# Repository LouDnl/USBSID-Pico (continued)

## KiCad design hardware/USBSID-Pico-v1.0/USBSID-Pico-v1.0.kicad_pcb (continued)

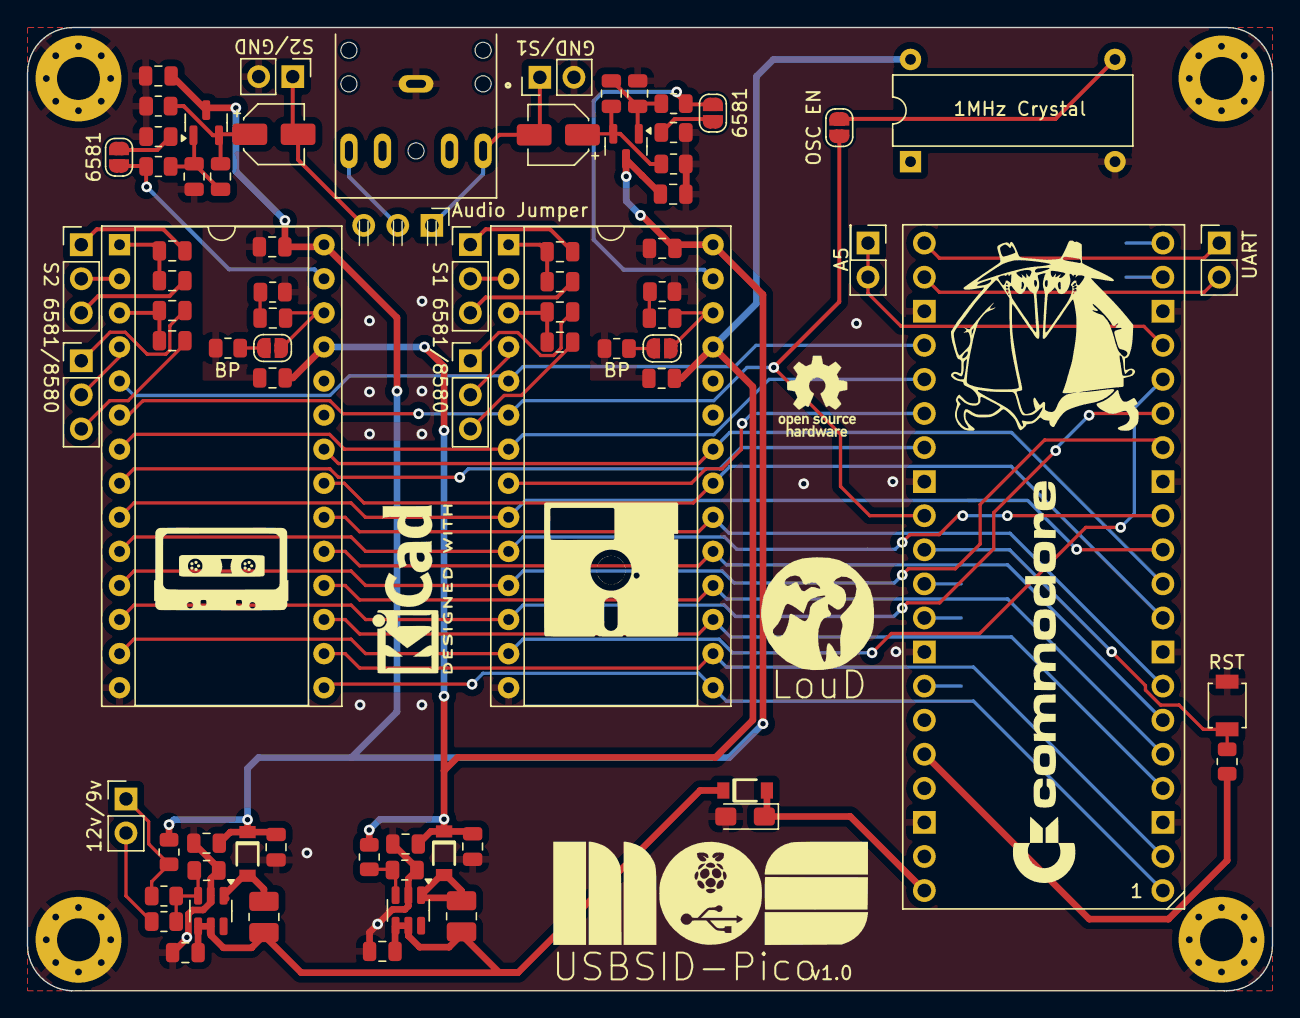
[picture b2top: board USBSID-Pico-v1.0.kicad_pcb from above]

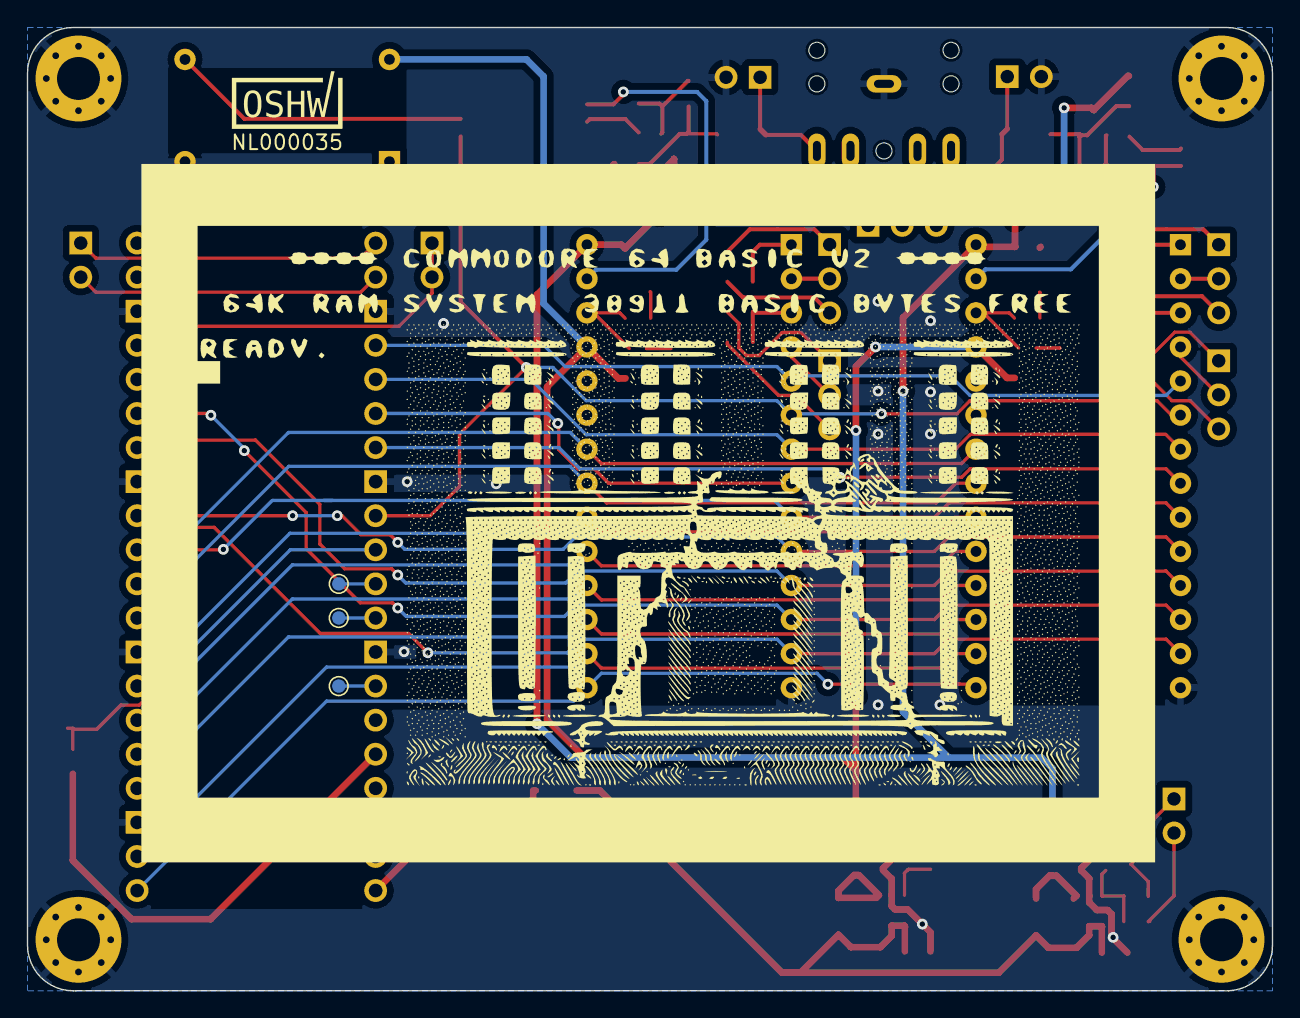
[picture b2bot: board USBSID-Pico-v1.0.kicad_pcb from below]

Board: 2 copper layers, 92.8 x 71.8 mm, 85 parts (5 on the bottom side), 73 nets.

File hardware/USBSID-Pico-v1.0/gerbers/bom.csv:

"Reference","Value","Mfg Qty","Mfg Part #","Manufacturer","Mfg Part Desc","Datasheet","Footprint","Optional Part #","Optional datasheet"
"TP1,TP2,TP3,TP4,TP5","-- mixed values --","","","","","~","TestPoint:TestPoint_Pad_D1.0mm","",""
"C1","10uF","1","T491A106K016AT","KEMET","10uF 16V 3Ω@100kHz ±10% CASE-A-3216-18(mm) Tantalum Capacitors","https://eu.mouser.com/datasheet/2/447/KEM_T2005_T491-3316937.pdf","Capacitor_Tantalum_SMD:CP_EIA-3216-10_Kemet-I_Pad1.58x1.35mm_HandSolder","",""
"C2,C4,C6,C8,C26,C27","470pF","1","0805B471K500NT","Guangdong Fenghua Advanced Tech","50V 470pF X7R ±10% 0805 Multilayer Ceramic Capacitors MLCC - SMD/SMT ROHS","https://www.lcsc.com/datasheet/lcsc_datasheet_2304140030_FH-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","Capacitor_SMD:C_0805_2012Metric","",""
"C3,C5,C7,C9","22nF","1","CL21B223KBANNNC","Samsung","50V 22nF X7R ±10% 0805 Multilayer Ceramic Capacitors MLCC - SMD/SMT ROHS","https://www.lcsc.com/datasheet/lcsc_datasheet_2304140030_Sam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","Capacitor_SMD:C_0805_2012Metric","",""
"C10,C11","1000pF","1","CL21B102KBANNNC","Samsung","50V 1nF X7R ±10% 0805 Multilayer Ceramic Capacitors MLCC - SMD/SMT ROHS","https://www.lcsc.com/datasheet/lcsc_datasheet_2304140030_Sam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","Capacitor_SMD:C_0805_2012Metric","",""
"C12,C13,C18,C19,C22,C23,C24,C25","100nF","1","CL21B104KBCNNNC","Samsung","50V 100nF X7R ±10% 0805 Multilayer Ceramic Capacitors MLCC - SMD/SMT ROHS","https://www.lcsc.com/datasheet/lcsc_datasheet_2304140030_Sam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","Capacitor_SMD:C_0805_2012Metric","",""
"C14,C15","10uF","1","RVT1E100M0405","Honor Elec","10uF 25V ±20% SMD,D4xL5.4mm Aluminum Electrolytic Capacitors - SMD ROHS","https://www.lcsc.com/datasheet/lcsc_datasheet_2304140030_Hon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","Capacitor_SMD:CP_Elec_4x5.3","",""
"C16,C17,C20,C21,C28,C29","22uF","1","CL21A226MAQNNNE","Samsung","25V 22uF X5R ±20% 0805 Multilayer Ceramic Capacitors MLCC - SMD/SMT ROHS","https://www.lcsc.com/datasheet/lcsc_datasheet_2304140030_Sam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","Capacitor_SMD:C_0805_2012Metric","",""
"D1,D2,D3","MBR120","1","MBR120VLSFT1G","onsemi","20V 300mV@1A 1A SOD-123FL Schottky Diodes ROHS","https://www.lcsc.com/datasheet/lcsc_datasheet_2210210200_ons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","LouD:SOD-123FL_diode","",""
"J1,J2","-- mixed values --","1","IC254V-12-28-0743-P1524","XFCN","28P DIP Round Hole -40℃~+105℃ 15.24mm 2.54mm DIP-28 IC / Transistor Socket ROHS","https://www.lcsc.com/datasheet/lcsc_datasheet_2108150330_XFC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","Package_DIP:DIP-28_W15.24mm_Socket","DS1010-32T1NX","https://www.lcsc.com/datasheet/lcsc_datasheet_1810281820_CON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"
"J5,J6,J7,J8","-- mixed values --","1","PH2.54-01-03PZD","XUNPU","Direct Insert Policy 2.5mm 6mm 3P -40℃~+105℃ 3mm 2.54mm Black Brass Single Row 1x3P Plugin,P=2.54mm Pin Headers ROHS","https://www.lcsc.com/datasheet/lcsc_datasheet_2401280925_XUN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","Connector_PinHeader_2.54mm:PinHeader_1x03_P2.54mm_Vertical","",""
"J9","Audio jumper","1","PH2.54-07-03PWD","XUNPU","Bend insert Policy 2.5mm 6mm 3P -40℃~+105℃ 2.54mm Black Brass Single Row 1x3P Push-Pull,P=2.54mm Pin Headers ROHS","https://www.lcsc.com/datasheet/lcsc_datasheet_2401281210_XUN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","Connector_PinHeader_2.54mm:PinHeader_1x03_P2.54mm_Horizontal","",""
"J11,J12,J13,J14,J16","-- mixed values --","1","PH2.54-01-02PZD","XUNPU","Direct Insert Policy 2.5mm 6mm 2P -40℃~+105℃ 3mm 2.54mm Black Brass Single Row 1x2P Plugin,P=2.54mm Pin Headers ROHS","https://www.lcsc.com/datasheet/lcsc_datasheet_2401281145_XUN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","-- mixed values --","",""
"J20","AudioJack2_Ground_Switch","1","SJ1-3525N","CuiDevices","Audio Jack with tip and ring switch","https://www.switchcraft.com/3-5mm-pc-horizontal-mount-jack-s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","LouD:3.5MM_SWITCHCRAFT_35RAPC4BHN2","PJ3F07-5P","https://www.lcsc.com/datasheet/lcsc_datasheet_2409272203_SHO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"
"L1,L2","4,7uH 1000mA","1","SPH252012H4R7MT","SunLord","1.25A 4.7uH ±20% 1.2A 1008 Power Inductors ROHS","https://www.lcsc.com/datasheet/lcsc_datasheet_2310251550_Sun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","Inductor_SMD:L_1008_2520Metric_Pad1.43x2.20mm_HandSolder","",""
"Q1,Q2","MMBT2222A","1","MMBT2222ALT1G","onsemi","40V 225mW 100@150mA,10V 600mA NPN SOT-23 Bipolar (BJT) ROHS","https://www.lcsc.com/datasheet/lcsc_datasheet_2304140030_ons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","Package_TO_SOT_SMD:SOT-23","",""
"R1,R4,R5","10k","1","0805W8F1002T5E","UNI-ROYAL","125mW Thick Film Resistors 150V ±100ppm/℃ ±1% 10kΩ 0805 Chip Resistor - Surface Mount ROHS","https://www.lcsc.com/datasheet/lcsc_datasheet_2206010216_UNI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","Resistor_SMD:R_0805_2012Metric","",""
"R2,R3,R6,R7,R8,R9,R15","1k","1","0805W8F1001T5E","-- mixed values --","-- mixed values --","https://www.lcsc.com/datasheet/lcsc_datasheet_2205311800_UNI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","Resistor_SMD:R_0805_2012Metric","",""
"R10","7,5k","1","0805W8F7501T5E","UNI-ROYAL","125mW Thick Film Resistors 150V ±100ppm/℃ ±1% 7.5kΩ 0805 Chip Resistor - Surface Mount ROHS","https://www.lcsc.com/datasheet/lcsc_datasheet_2205311830_UNI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","Resistor_SMD:R_0805_2012Metric","",""
"R11","18k","1","0805W8F1802T5E","UNI-ROYAL","125mW Thick Film Resistors 150V ±100ppm/℃ ±1% 18kΩ 0805 Chip Resistor - Surface Mount ROHS","https://www.lcsc.com/datasheet/lcsc_datasheet_2206010216_UNI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","Resistor_SMD:R_0805_2012Metric","",""
"R12","47k","1","0805W8F4702T5E","UNI-ROYAL","125mW Thick Film Resistors 150V ±100ppm/℃ ±1% 47kΩ 0805 Chip Resistor - Surface Mount ROHS","https://www.lcsc.com/datasheet/lcsc_datasheet_2206010200_UNI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","Resistor_SMD:R_0805_2012Metric","",""
"R13,R14","100k","1","0805W8F1003T5E","UNI-ROYAL","125mW Thick Film Resistors 150V ±100ppm/℃ ±1% 100kΩ 0805 Chip Resistor - Surface Mount ROHS","https://www.lcsc.com/datasheet/lcsc_datasheet_2205312316_UNI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","Resistor_SMD:R_0805_2012Metric","",""
"R16,R17","330k","1","0805W8F3303T5E","UNI-ROYAL","125mW Thick Film Resistors 150V ±100ppm/℃ ±1% 330kΩ 0805 Chip Resistor - Surface Mount ROHS","https://www.lcsc.com/datasheet/lcsc_datasheet_2205311830_UNI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","Resistor_SMD:R_0805_2012Metric","",""
"SW1","RST","1","B3U-1000P","Omron Electronics","2.5mm 1.6mm Round Button 50mA Standing paste 3mm SPST 153gf 12V SMD,2.5x3mm Tactile Switches ROHS","https://eu.mouser.com/datasheet/2/307/en-b3u-3615.pdf","LouD:SW_SPST_B3U-1000P_larger_pads","",""
"U2,U3","MT3608","1","MT3608","AeroSemi","High Efficiency 1.2MHz 2A Step Up Converter","https://www.olimex.com/Products/Breadboarding/BB-PWR-3608/re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","Package_TO_SOT_SMD:SOT-23-6","",""
"U1","Pico","2","PM254-1-20-Z-8.5","HCTL","2.54mm Single Row 3A Brass Alloy 20P","https://www.lcsc.com/datasheet/lcsc_datasheet_2306091006_HCT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","LouD:RPi_Pico_TH_PinRows_Only","",""

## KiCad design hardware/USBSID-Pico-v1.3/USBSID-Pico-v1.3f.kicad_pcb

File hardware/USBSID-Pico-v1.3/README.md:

# USBSID-Pico v1.3 PCB design files
This directory contains the open source KiCad design files for v1.3 of the USBSID-Pico pcb.  

# Gerbers
The gerber files are in the [gerbers](gerbers/) directory.

# OSHWA certification
  
[OSHW] NL000045 | Certified open source hardware | [oshwa.org/cert](https://certification.oshwa.org/nl000045.html)

# Disclaimer
I do this stuff in my free time for my enjoyment. Since I like to share my joy in creating this with everyone I try my best to provide a working PCB and Firmware. I am in no way an electronics engineer and can give __no guarantees__ that this stuff does not break or damage your hardware, computer, phone, or whatever you try to hook it up to. Be sure to take great care when inserting any real MOS SID chips into the board. While everything has been tested with real chips, this is in no way a guarantee that nothing could go wrong. Use of this board and firmware at your own risk! I am in no way responsible for your damaged hardware. That being said, have fun!

# License
### Software License ~ GNUv2
All code written by me in this repository is licensed under the terms of the GNU General Public License as published by the Free Software Foundation, version 2.
Any code in this repository that is not written by me automatically falls under the licensing conditions by the authors of said code as mentioned in the source code header.
For for more information about this license please read the LICENSE document in the root of the USBSID-Pico repository.
### USBSID-Pico v1.3 PCB Hardware License ~ CC BY-SA 4.0
<a href="https://github.com/LouDnl/USBSID-Pico/tree/master/hardware/USBSID-Pico-v1.3">USBSID-Pico v1.3 PCB</a> © 2025-2026 by <a href="https://github.com/LouDnl">LouD</a> is licensed under <a href="https://creativecommons.org/licenses/by-sa/4.0/">Creative Commons Attribution-ShareAlike 4.0 International</a>

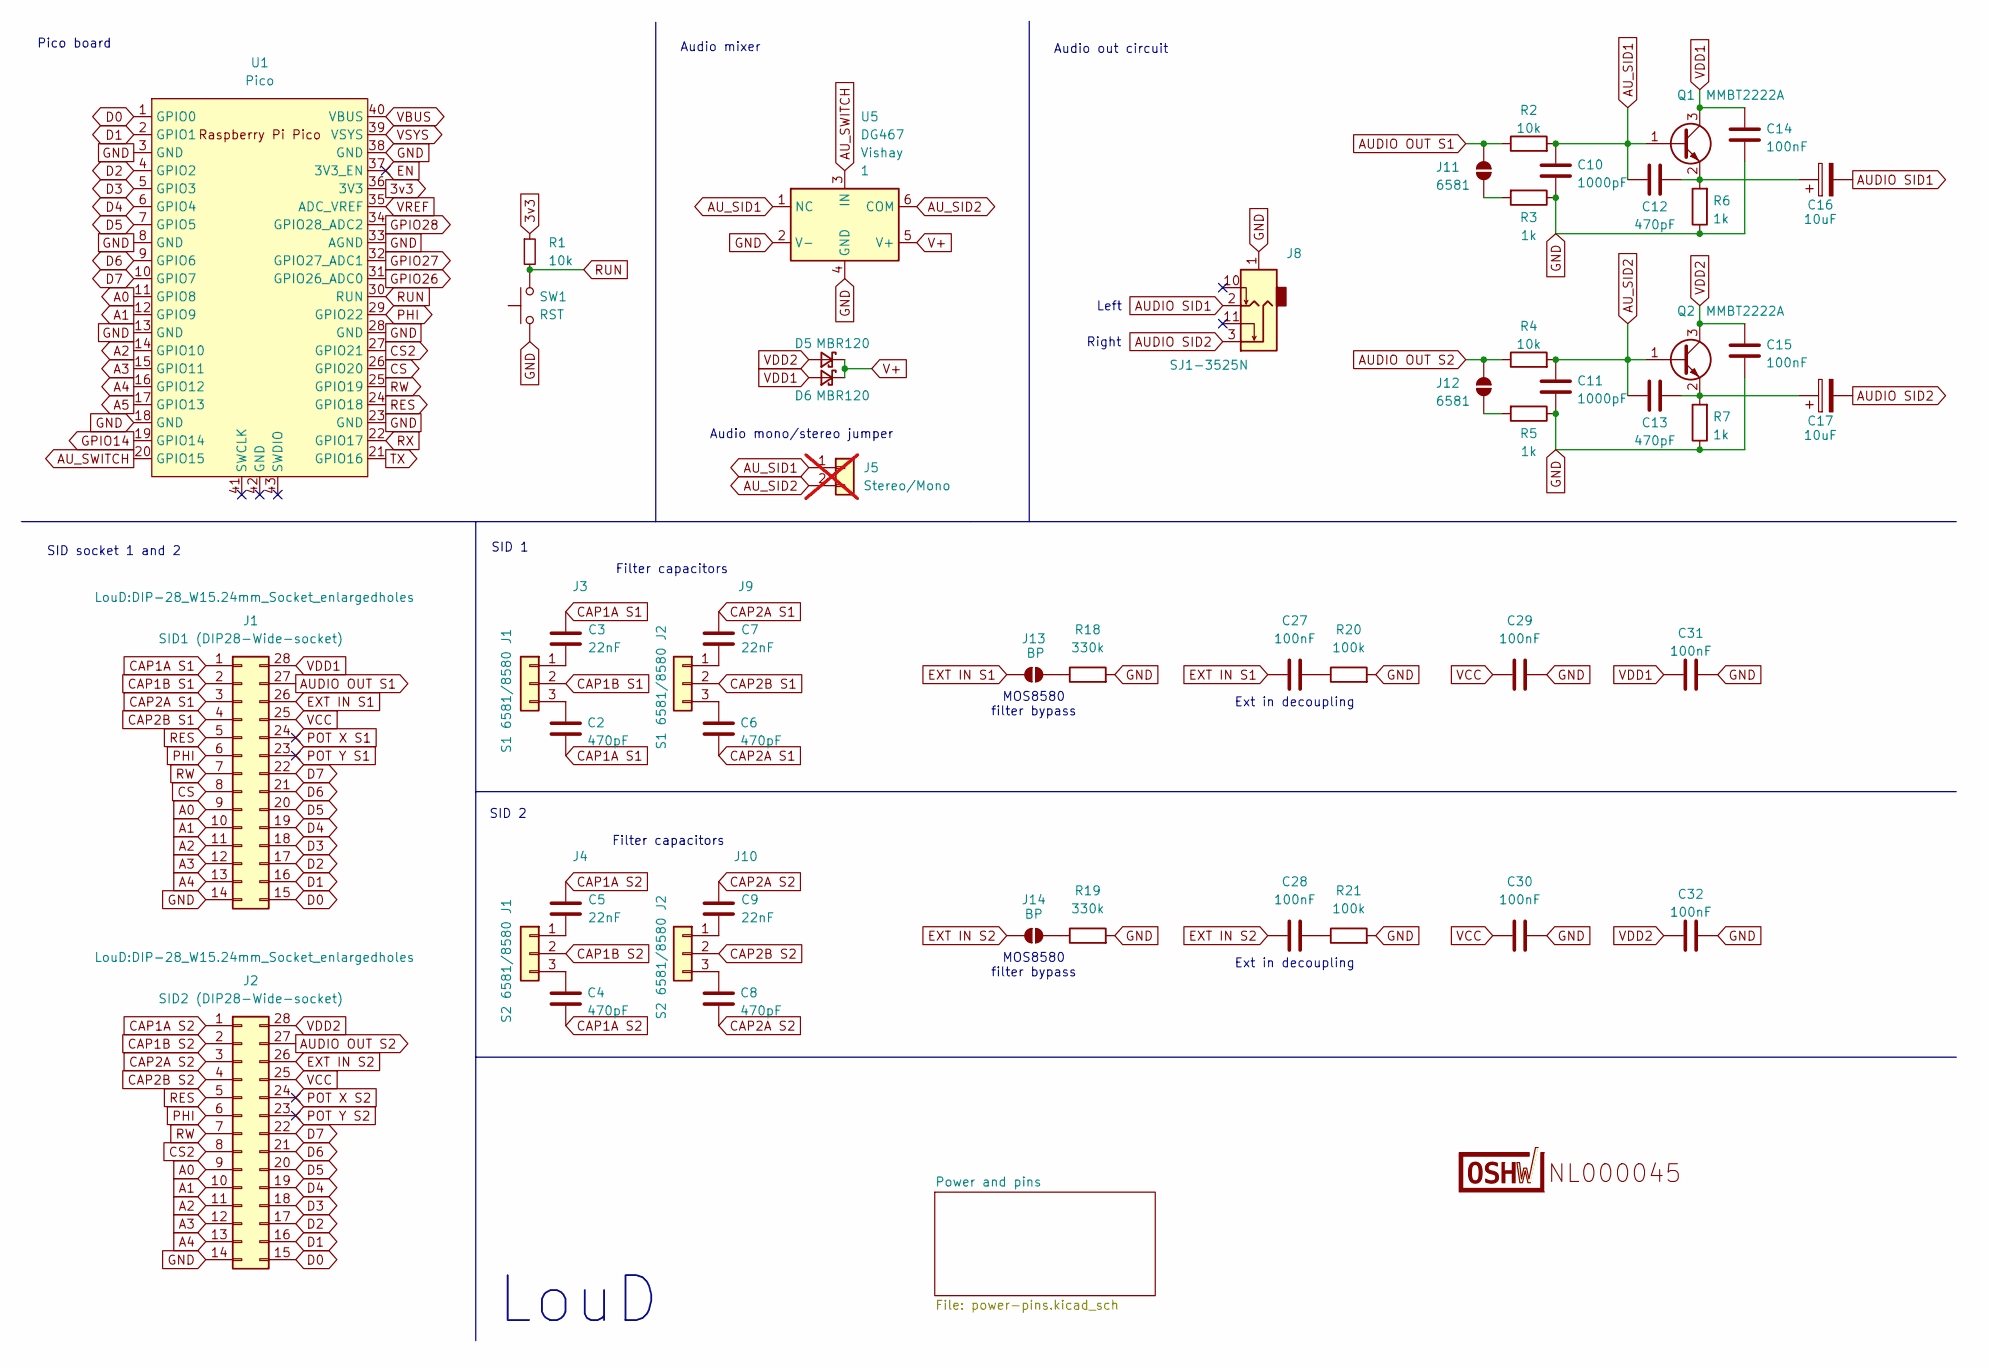
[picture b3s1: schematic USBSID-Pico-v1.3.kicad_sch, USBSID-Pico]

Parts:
C2, C4, C6, C8, C12, C13: 470pF; C_0805_2012Metric; Mfg Part # 0805B471K500NT
C3, C5, C7, C9: 22nF; C_0805_2012Metric; Mfg Part # CL21B223KBANNNC
C10, C11: 1000pF; C_0805_2012Metric; Mfg Part # CL21B102KBANNNC
C14, C15, C27, C28, C29, C30, C31, C32: 100nF; C_0805_2012Metric; Mfg Part # CL21B104KBCNNNC
C16, C17: 10uF; CP_Elec_4x5.3; Mfg Part # RVT1E100M0405
D5, D6: MBR120; SOD-123FL_diode; Mfg Part # MBR120VLSFT1G
J1: SID1 (DIP28-Wide-socket); DIP-28_W15.24mm_Socket_enlargedholes; Mfg Part # DS1009-28AT1WX-0A2
J2: SID2 (DIP28-Wide-socket); DIP-28_W15.24mm_Socket_enlargedholes; Mfg Part # DS1009-28AT1WX-0A2
J3: S1 6581/8580 J1; PinHeader_1x03_P2.54mm_Horizontal; Mfg Part # HX PZ2.54-1x3P WZ
J4: S2 6581/8580 J1; PinHeader_1x03_P2.54mm_Horizontal; Mfg Part # HX PZ2.54-1x3P WZ
J5: Stereo/Mono; PinHeader_1x02_P2.54mm_Horizontal; Mfg Part # PH2.54-01-02PZD; not fitted
J8: SJ1-3525N; 3.5MM_SWITCHCRAFT_35RAPC4BHN2; Mfg Part # SJ1-3525N
J9: S1 6581/8580 J2; PinHeader_1x03_P2.54mm_Horizontal; Mfg Part # HX PZ2.54-1x3P WZ
J10: S2 6581/8580 J2; PinHeader_1x03_P2.54mm_Horizontal; Mfg Part # HX PZ2.54-1x3P WZ
J11, J12: 6581; SolderJumper-2_P1.3mm_Open_RoundedPad1.0x1.5mm
J13, J14: BP; SolderJumper-2_P1.3mm_Open_RoundedPad1.0x1.5mm
LOGO1: (no value)
Q1, Q2: MMBT2222A; SOT-23; Mfg Part # MMBT2222ALT1G
R1, R2, R4: 10k; R_0805_2012Metric; Mfg Part # 0805W8F1002T5E
R3, R5, R6, R7: 1k; R_0805_2012Metric; Mfg Part # 0805W8F1001T5E
R18, R19: 330k; R_0805_2012Metric; Mfg Part # 0805W8F3303T5E
R20, R21: 100k; R_0805_2012Metric; Mfg Part # 0805W8F1003T5E
SW1: RST; SW_SPST_B3U-1000P_larger_pads; Mfg Part # B3U-1000P
U1: Pico; RPi_Pico_SMD_TH_noholes; Mfg Part # PM254-1-20-Z-8.5
U5: DG467; SOT-23-6; Mfg Part Desc Low Power, High Voltage SPST Analog Swi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

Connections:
3v3: R1.1, U1.36 (3V3)
A0: J1.9, J2.9, U1.11 (GPIO8)
A1: J1.10, J2.10, U1.12 (GPIO9)
A2: J1.11, J2.11, U1.14 (GPIO10)
A3: J1.12, J2.12, U1.15 (GPIO11)
A4: J1.13, J2.13, U1.16 (GPIO12)
A5: U1.17 (GPIO13); also elsewhere on the board
AUDIO OUT S1: J1.27, J11.1 (A), R2.1
AUDIO OUT S2: J2.27, J12.1 (A), R4.1
AUDIO SID1: C16.2, J8.2; also elsewhere on the board
AUDIO SID2: C17.2, J8.3; also elsewhere on the board
AU_SID1: C10.1, C12.2, J5.1, Q1.1 (B), R2.2, U5.1 (NC)
AU_SID2: C11.1, C13.2, J5.2, Q2.1 (B), R4.2, U5.6 (COM)
AU_SWITCH: U1.20 (GPIO15), U5.3 (IN); also elsewhere on the board
CAP1A S1: C2.1, C3.2, J1.1
CAP1A S2: C4.1, C5.2, J2.1
CAP1B S1: J1.2, J3.2
CAP1B S2: J2.2, J4.2
CAP2A S1: C6.1, C7.2, J1.3
CAP2A S2: C8.1, C9.2, J2.3
CAP2B S1: J1.4, J9.2
CAP2B S2: J2.4, J10.2
CS: J1.8, U1.26 (GPIO20)
CS2: J2.8, U1.27 (GPIO21)
D0: J1.15, J2.15, U1.1 (GPIO0)
D1: J1.16, J2.16, U1.2 (GPIO1)
D2: J1.17, J2.17, U1.4 (GPIO2)
D3: J1.18, J2.18, U1.5 (GPIO3)
D4: J1.19, J2.19, U1.6 (GPIO4)
D5: J1.20, J2.20, U1.7 (GPIO5)
D6: J1.21, J2.21, U1.9 (GPIO6)
D7: J1.22, J2.22, U1.10 (GPIO7)
EN: U1.37 (3V3_EN)
EN_1: U1.37 (3V3_EN)
EXT IN S1: C27.1, J1.26, J13.2 (B); also elsewhere on the board
EXT IN S2: C28.1, J2.26, J14.2 (B); also elsewhere on the board
GND: C10.2, C11.2, C14.2, C15.2, C29.2, C30.2, C31.1, C32.1, J1.14, J2.14, J8.1, R3.1, R5.1, R6.1, R7.1, R18.2, R19.2, R20.2, R21.2, SW1.1, U1.3 (GND), U1.8 (GND), U1.13 (GND), U1.18 (GND), U1.23 (GND), U1.28 (GND), U1.33 (AGND), U1.38 (GND), U5.2 (V-), U5.4 (GND); also elsewhere on the board
GPIO14: U1.19 (GPIO14); also elsewhere on the board
GPIO26: U1.31 (GPIO26_ADC0); also elsewhere on the board
GPIO27: U1.32 (GPIO27_ADC1); also elsewhere on the board
GPIO28: U1.34 (GPIO28_ADC2); also elsewhere on the board
unnamed: C27.2, R20.1
unnamed: C28.2, R21.1
unnamed: C3.1, J3.1
unnamed: C2.2, J3.3
unnamed: C5.1, J4.1
unnamed: C4.2, J4.3
unnamed: C7.1, J9.1
unnamed: C6.2, J9.3
unnamed: C9.1, J10.1
unnamed: C8.2, J10.3
unnamed: J11.2 (B), R3.2
unnamed: J12.2 (B), R5.2
unnamed: J13.1 (A), R18.1
unnamed: J14.1 (A), R19.1
unnamed: C12.1, C16.1, Q1.2 (E), R6.2
unnamed: C13.1, C17.1, Q2.2 (E), R7.2
PHI: J1.6, J2.6, U1.29 (GPIO22)
POT X S1: J1.24
POT X S2: J2.24
POT Y S1: J1.23
POT Y S2: J2.23
RES: J1.5, J2.5, U1.24 (GPIO18)
RUN: R1.2, SW1.2, U1.30 (RUN)
RW: J1.7, J2.7, U1.25 (GPIO19)
RX: U1.22 (GPIO17); also elsewhere on the board
TX: U1.21 (GPIO16); also elsewhere on the board
V+: D5.1 (K), D6.1 (K), U5.5 (V+)
VBUS: U1.40 (VBUS); also elsewhere on the board
VCC: C29.1, C30.1, J1.25, J2.25; also elsewhere on the board
VDD1: C14.1, C31.2, D6.2 (A), J1.28, Q1.3 (C); also elsewhere on the board
VDD2: C15.1, C32.2, D5.2 (A), J2.28, Q2.3 (C); also elsewhere on the board
VREF: U1.35 (ADC_VREF)
VSYS: U1.39 (VSYS)

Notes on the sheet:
Left
SID socket 1 and 2
SID 1
Filter capacitors
Pico board
Right
Audio mixer
LouD
Ext in decoupling
SID 2
Audio out circuit
Audio mono/stereo jumper
MOS8580 filter bypass

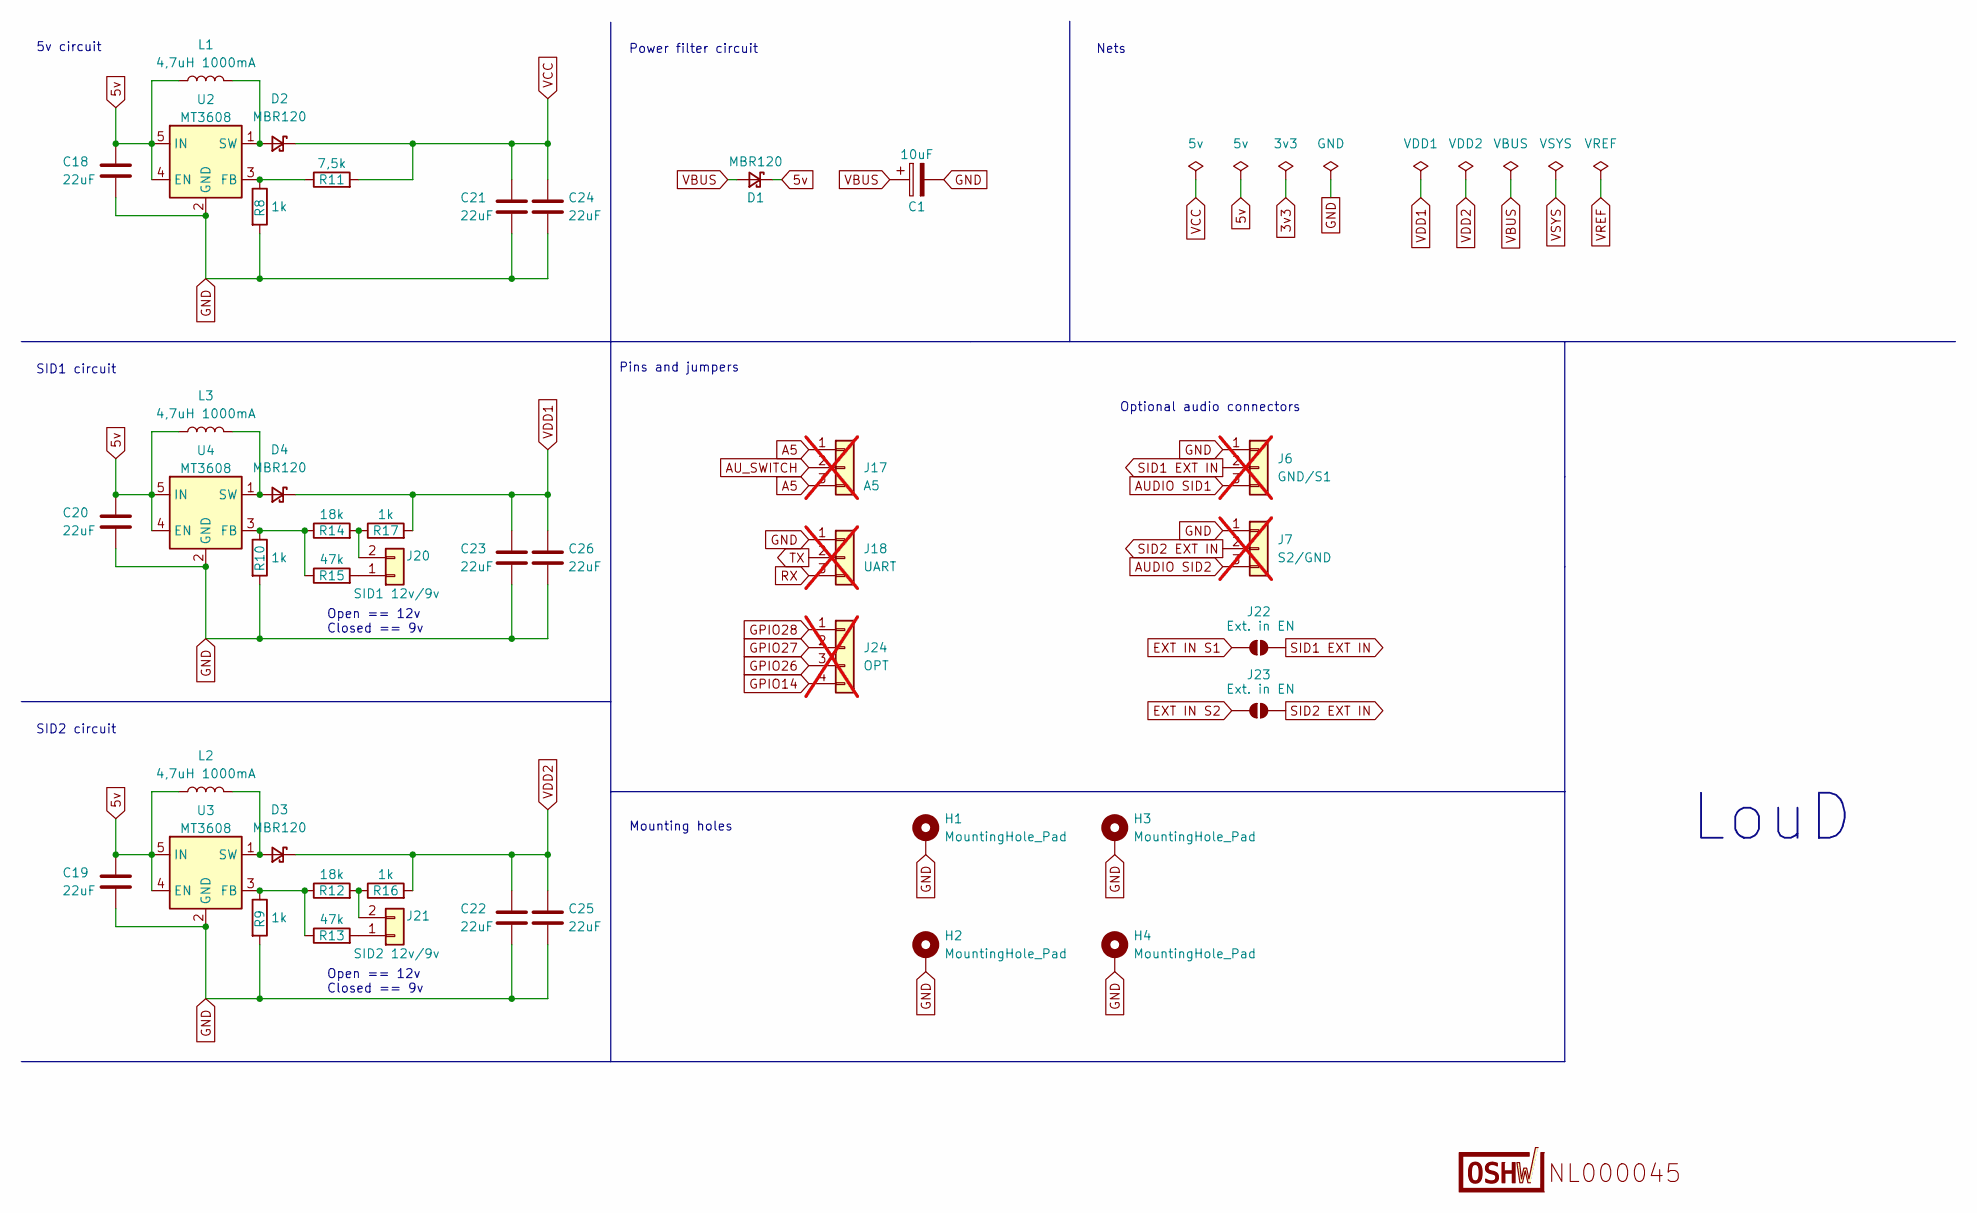
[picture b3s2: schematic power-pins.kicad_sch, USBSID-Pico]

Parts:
C1: 10uF; CP_EIA-3216-10_Kemet-I_Pad1.58x1.35mm_HandSolder; Mfg Part # T491A106K016AT
C18, C19, C20, C21, C22, C23, C24, C25, C26: 22uF; C_0805_2012Metric; Mfg Part # CL21A226MAQNNNE
D1, D2, D3, D4: MBR120; SOD-123FL_diode; Mfg Part # MBR120VLSFT1G
H1, H2, H3, H4: MountingHole_Pad; MountingHole_3.2mm_M3_Pad_Via
J6: GND/S1; PinHeader_1x03_P2.54mm_Vertical; Mfg Part # PH2.54-01-03PZD; not fitted
J7: S2/GND; PinHeader_1x03_P2.54mm_Vertical; Mfg Part # PH2.54-01-03PZD; not fitted
J17: A5; PinHeader_1x03_P2.54mm_Horizontal; Mfg Part # HX PZ2.54-1x3P WZ; not fitted
J18: UART; PinHeader_1x03_P2.54mm_Vertical; Mfg Part # PH2.54-01-03PZD; not fitted
J20: SID1 12v/9v; PinHeader_1x02_P2.54mm_Vertical; Mfg Part # PH2.54-01-02PZD
J21: SID2 12v/9v; PinHeader_1x02_P2.54mm_Vertical; Mfg Part # PH2.54-01-02PZD
J22, J23: Ext. in EN; SolderJumper-2_P1.3mm_Open_RoundedPad1.0x1.5mm
J24: OPT; PinHeader_1x04_P2.54mm_Vertical; Mfg Part # PH2.54-01-02PZD; not fitted
L1, L2, L3: 4,7uH 1000mA; L_1008_2520Metric_Pad1.43x2.20mm_HandSolder; Mfg Part # SPH252012H4R7MT
LOGO2: (no value)
R8, R9, R10, R16, R17: 1k; R_0805_2012Metric; Mfg Part # 0805W8F1001T5E
R11: 7,5k; R_0805_2012Metric; Mfg Part # 0805W8F7501T5E
R12, R14: 18k; R_0805_2012Metric; Mfg Part # 0805W8F1802T5E
R13, R15: 47k; R_0805_2012Metric; Mfg Part # 0805W8F4702T5E
U2, U3, U4: MT3608; SOT-23-6; Mfg Part # MT3608

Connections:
5v: C18.1, C19.1, C20.1, D1.1 (K), L1.1, L2.1, L3.1, U2.4 (EN), U2.5 (IN), U3.4 (EN), U3.5 (IN), U4.4 (EN), U4.5 (IN)
A5: J17.1, J17.3; also elsewhere on the board
AUDIO SID1: J6.3; also elsewhere on the board
AUDIO SID2: J7.3; also elsewhere on the board
AU_SWITCH: J17.2; also elsewhere on the board
EXT IN S1: J22.2 (B); also elsewhere on the board
EXT IN S2: J23.2 (B); also elsewhere on the board
GND: C1.2, C18.2, C19.2, C20.2, C21.2, C22.2, C23.2, C24.2, C25.2, C26.2, H1.1, H2.1, H3.1, H4.1, J6.1, J7.1, J18.1, R8.2, R9.2, R10.2, U2.2 (GND), U3.2 (GND), U4.2 (GND); also elsewhere on the board
GPIO14: J24.4; also elsewhere on the board
GPIO26: J24.3; also elsewhere on the board
GPIO27: J24.2; also elsewhere on the board
GPIO28: J24.1; also elsewhere on the board
unnamed: D2.2 (A), L1.2, U2.1 (SW)
unnamed: D3.2 (A), L2.2, U3.1 (SW)
unnamed: D4.2 (A), L3.2, U4.1 (SW)
unnamed: J20.1, R15.2
unnamed: J20.2, R14.2, R17.1
unnamed: J21.1, R13.2
unnamed: J21.2, R12.2, R16.1
unnamed: R8.1, R11.1, U2.3 (FB)
unnamed: R9.1, R12.1, R13.1, U3.3 (FB)
unnamed: R10.1, R14.1, R15.1, U4.3 (FB)
RX: J18.3; also elsewhere on the board
SID1 EXT IN: J6.2, J22.1 (A)
SID2 EXT IN: J7.2, J23.1 (A)
TX: J18.2; also elsewhere on the board
VBUS: C1.1, D1.2 (A); also elsewhere on the board
VCC: C21.1, C24.1, D2.1 (K), R11.2; also elsewhere on the board
VDD1: C23.1, C26.1, D4.1 (K), R17.2; also elsewhere on the board
VDD2: C22.1, C25.1, D3.1 (K), R16.2; also elsewhere on the board

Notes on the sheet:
5v circuit
LouD
Pins and jumpers
Power filter circuit
Nets
Open == 12v Closed == 9v
Mounting holes
SID2 circuit
SID1 circuit
Optional audio connectors
